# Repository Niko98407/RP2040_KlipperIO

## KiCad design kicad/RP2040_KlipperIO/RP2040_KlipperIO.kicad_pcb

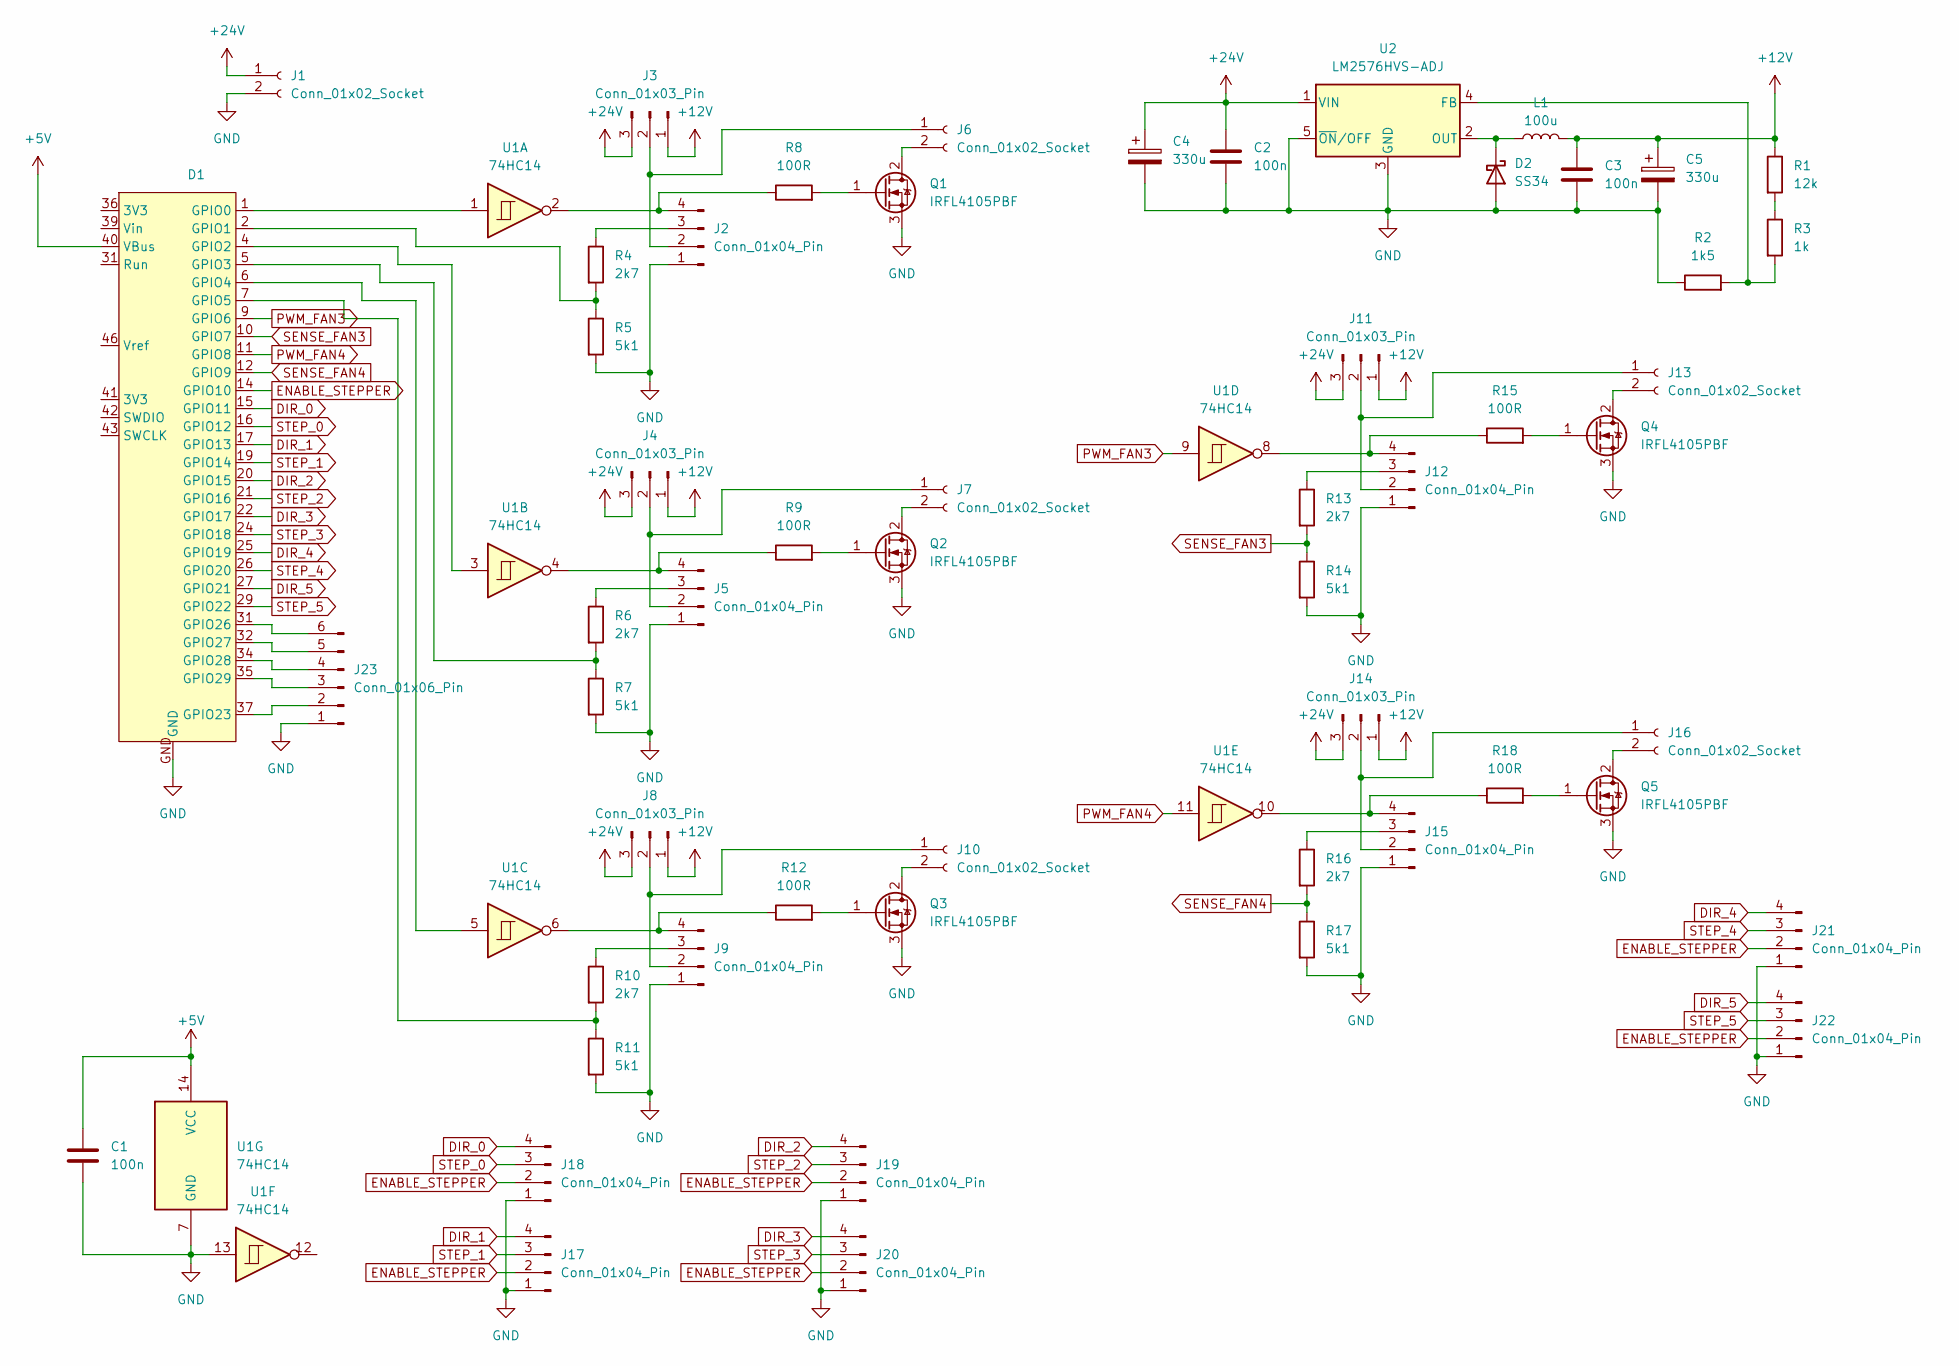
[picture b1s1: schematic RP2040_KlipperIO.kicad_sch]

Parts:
C1, C2, C3: 100n; C_0603_1608Metric_Pad1.08x0.95mm_HandSolder
C4, C5: 330u; CP_Elec_10x7.9
D1: RaspberryPi_Pico_2040
D2: SS34; D_SMA_Handsoldering
J1, J6, J7, J10, J13, J16: Conn_01x02_Socket; TerminalBlock_RND_205-00001_1x02_P5.00mm_Horizontal
J2, J5, J9, J12, J15: Conn_01x04_Pin; Molex_KK-254_AE-6410-04A_1x04_P2.54mm_Vertical
J3, J4, J8, J11, J14: Conn_01x03_Pin; PinHeader_1x03_P2.54mm_Vertical
J17, J18, J19, J20, J21, J22: Conn_01x04_Pin; TerminalBlock_RND_205-00003_1x04_P5.00mm_Horizontal
J23: Conn_01x06_Pin; TerminalBlock_RND_205-00005_1x06_P5.00mm_Horizontal
L1: 100u; L_12x12mm_H8mm
Q1, Q2, Q3, Q4, Q5: IRFL4105PBF; SOT-223
R1: 12k; R_0603_1608Metric_Pad0.98x0.95mm_HandSolder
R2: 1k5; R_0603_1608Metric_Pad0.98x0.95mm_HandSolder
R3: 1k; R_0603_1608Metric_Pad0.98x0.95mm_HandSolder
R4, R6, R10, R13, R16: 2k7; R_0603_1608Metric_Pad0.98x0.95mm_HandSolder
R5, R7, R11, R14, R17: 5k1; R_0603_1608Metric_Pad0.98x0.95mm_HandSolder
R8, R9, R12, R15, R18: 100R; R_0603_1608Metric_Pad0.98x0.95mm_HandSolder
U1: 74HC14; SOIC-14_3.9x8.7mm_P1.27mm
U2: LM2576HVS-ADJ; TO-263-5_TabPin3

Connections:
+5V: C1.1, D1.40 (VBus), U1.14 (VCC)
+12V: C3.1, C5.1, J3.1, J4.1, J8.1, J11.1, J14.1, L1.2, R1.1
+24V: C2.1, C4.1, J1.1, J3.3, J4.3, J8.3, J11.3, J14.3, U2.1 (VIN)
DIR_0: D1.15 (GPIO11), J18.4
DIR_1: D1.17 (GPIO13), J17.4
DIR_2: D1.20 (GPIO15), J19.4
DIR_3: D1.22 (GPIO17), J20.4
DIR_4: D1.25 (GPIO19), J21.4
DIR_5: D1.27 (GPIO21), J22.4
ENABLE_STEPPER: D1.14 (GPIO10), J17.2, J18.2, J19.2, J20.2, J21.2, J22.2
GND: C1.2, C2.2, C3.2, C4.2, C5.2, D1.GND, D2.2 (A), J1.2, J2.1, J5.1, J9.1, J12.1, J15.1, J17.1, J18.1, J19.1, J20.1, J21.1, J22.1, J23.1, Q1.3 (S), Q2.3 (S), Q3.3 (S), Q4.3 (S), Q5.3 (S), R2.1, R5.2, R7.2, R11.2, R14.2, R17.2, U1.7 (GND), U1.13, U2.3 (GND), U2.5 (~ON/OFF)
unnamed: D1.1 (GPIO0), U1.1
unnamed: D1.2 (GPIO1), R4.2, R5.1
unnamed: D1.4 (GPIO2), U1.3
unnamed: D1.5 (GPIO3), R6.2, R7.1
unnamed: D1.6 (GPIO4), U1.5
unnamed: D1.7 (GPIO5), R10.2, R11.1
unnamed: D1.37 (GPIO23), J23.2
unnamed: D1.31 (GPIO26), J23.6
unnamed: D1.32 (GPIO27), J23.5
unnamed: D1.34 (GPIO28), J23.4
unnamed: D1.35 (GPIO29), J23.3
unnamed: D2.1 (K), L1.1, U2.2 (OUT)
unnamed: J2.2, J3.2, J6.1
unnamed: J2.3, R4.1
unnamed: J2.4, R8.1, U1.2
unnamed: J4.2, J5.2, J7.1
unnamed: J5.3, R6.1
unnamed: J5.4, R9.1, U1.4
unnamed: J6.2, Q1.2 (D)
unnamed: J7.2, Q2.2 (D)
unnamed: J9.3, R10.1
unnamed: J9.4, R12.1, U1.6
unnamed: J8.2, J9.2, J10.1
unnamed: J10.2, Q3.2 (D)
unnamed: J11.2, J12.2, J13.1
unnamed: J12.3, R13.1
unnamed: J12.4, R15.1, U1.8
unnamed: J13.2, Q4.2 (D)
unnamed: J14.2, J15.2, J16.1
unnamed: J15.3, R16.1
unnamed: J15.4, R18.1, U1.10
unnamed: J16.2, Q5.2 (D)
unnamed: Q1.1 (G), R8.2
unnamed: Q2.1 (G), R9.2
unnamed: Q3.1 (G), R12.2
unnamed: Q4.1 (G), R15.2
unnamed: Q5.1 (G), R18.2
unnamed: R1.2, R3.1
unnamed: R2.2, R3.2, U2.4 (FB)
PWM_FAN3: D1.9 (GPIO6), U1.9
PWM_FAN4: D1.11 (GPIO8), U1.11
SENSE_FAN3: D1.10 (GPIO7), R13.2, R14.1
SENSE_FAN4: D1.12 (GPIO9), R16.2, R17.1
STEP_0: D1.16 (GPIO12), J18.3
STEP_1: D1.19 (GPIO14), J17.3
STEP_2: D1.21 (GPIO16), J19.3
STEP_3: D1.24 (GPIO18), J20.3
STEP_4: D1.26 (GPIO20), J21.3
STEP_5: D1.29 (GPIO22), J22.3

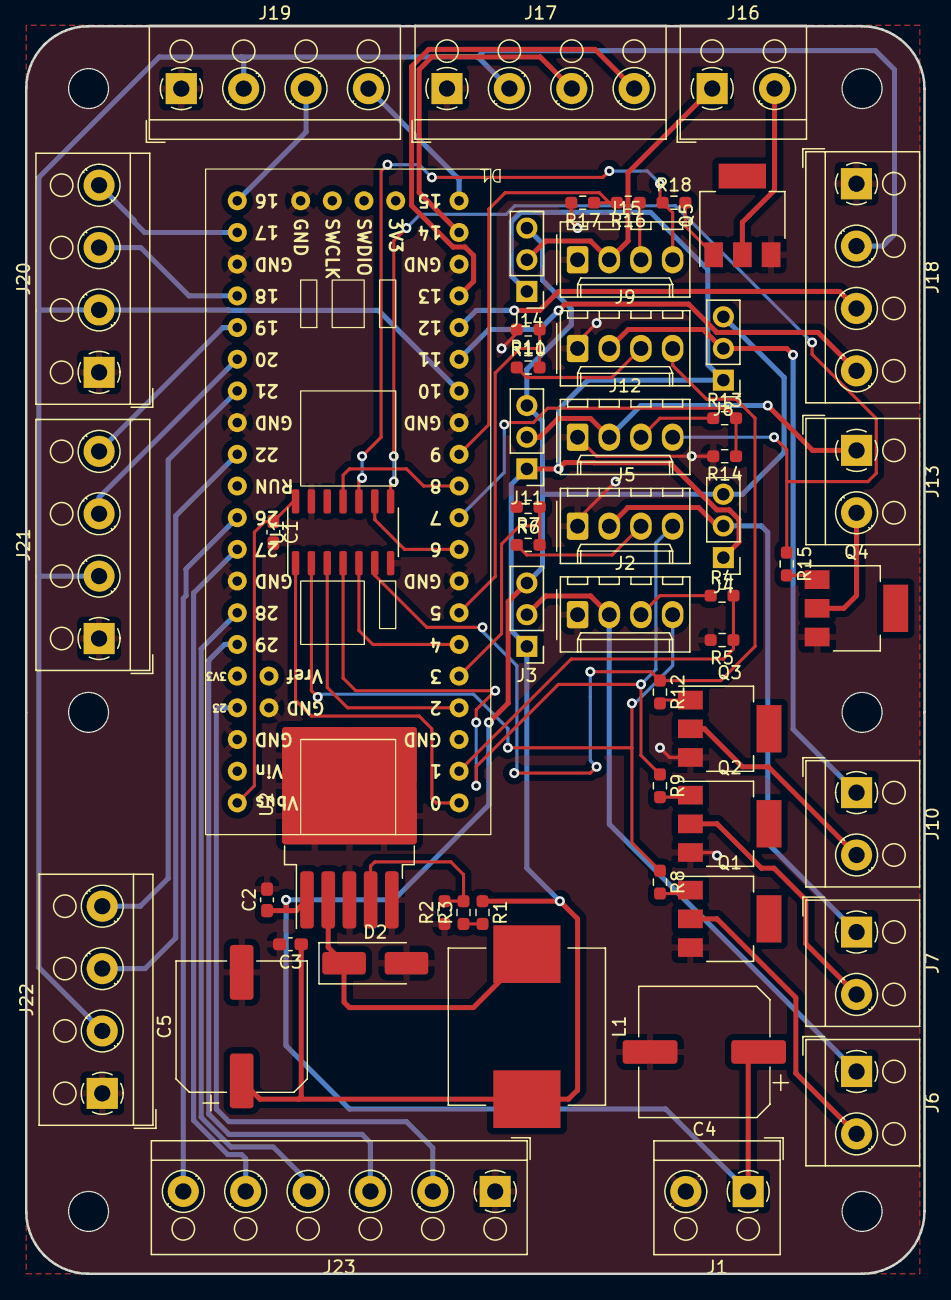
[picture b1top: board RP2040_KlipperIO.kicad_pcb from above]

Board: 2 copper layers, 72.0 x 100.0 mm, 56 parts (0 on the bottom side), 60 nets.

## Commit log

2024-04-09 add project
2024-04-12 Add basic schematic
2024-04-12 route pcb
